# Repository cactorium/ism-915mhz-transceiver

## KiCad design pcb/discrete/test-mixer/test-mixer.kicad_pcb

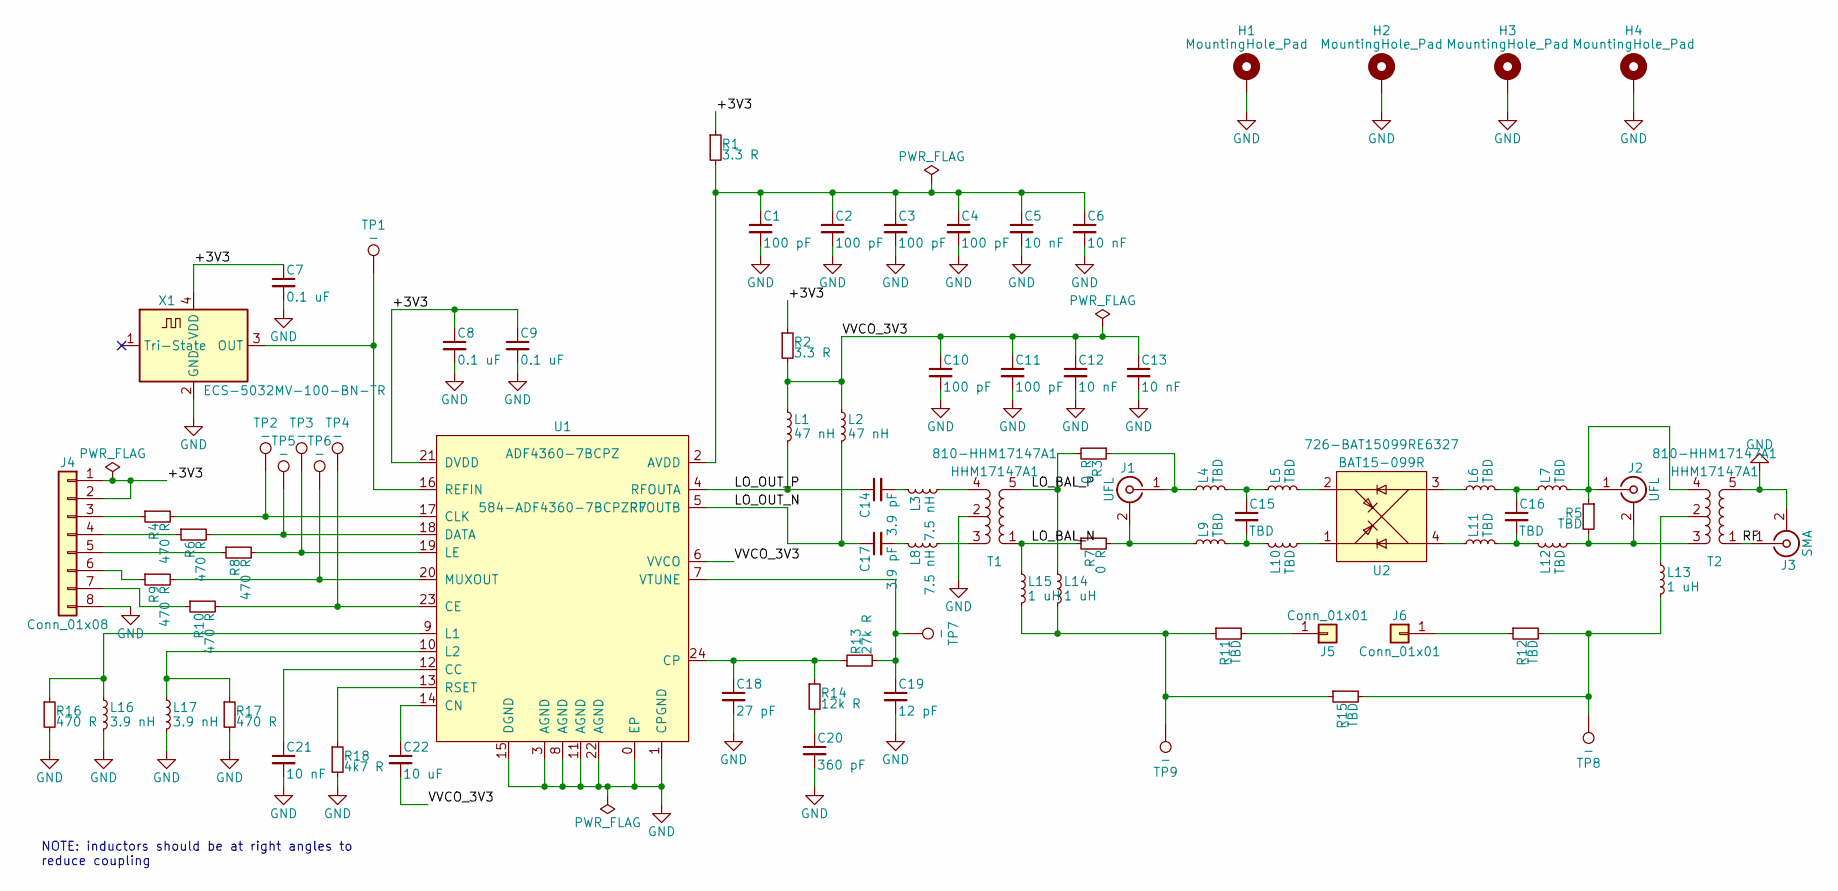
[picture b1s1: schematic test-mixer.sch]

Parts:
C1, C2, C3, C4, C10, C11: 100 pF; C_0603_1608Metric_Pad1.05x0.95mm_HandSolder; Mouser 791-RF18N101J500CT
C5, C6, C12, C13, C21: 10 nF; C_0402_1005Metric; Mouser 80-C0402C103K4R7411
C7, C8, C9: 0.1 uF; C_0402_1005Metric; Mouser 80-C0402C104M4P
C14, C17: 3.9 pF; C_0402_1005Metric; Mouser 81-GJM1555C1H3R9CB1D
C15, C16: TBD; C_0402_1005Metric; Mouser NoPart
C18: 27 pF; C_0603_1608Metric_Pad1.05x0.95mm_HandSolder; Mouser 80-C0603C270K5G
C19: 12 pF; C_0805_2012Metric_Pad1.15x1.40mm_HandSolder; Mouser 80-C0805C120J1HACTU
C20: 360 pF; C_0402_1005Metric; Mouser 963-UMK105CH361JVHF
C22: 10 uF; C_0805_2012Metric_Pad1.15x1.40mm_HandSolder; Mouser 81-GRM21BC81C106KE5L
H1, H2, H3, H4: MountingHole_Pad; MountingHole_3.2mm_M3_DIN965; Mouser NoPart
J1, J2: UFL; 2337019-1; Mouser 571-2337019-1
J3: SMA; 142-0701-801-with-taper; Mouser 530-142-0701-801
J4: Conn_01x08; PinHeader_1x08_P2.54mm_Vertical; Mouser NoPart
J5, J6: Conn_01x01; PinSocket_1x01_P2.54mm_Vertical; Mouser NoPart
L1, L2: 47 nH; C_0402_1005Metric; Mouser 81-LQG15HZ47NJ02D
L3, L8: 7.5 nH; C_0402_1005Metric; Mouser 81-LQG15HN7N5J02D
L4, L5, L6, L7, L9, L10, L11, L12: TBD; C_0402_1005Metric; Mouser NoPart
L13, L14, L15: 1 uH; C_0402_1005Metric; Mouser 815-AIML-0402-1R0KT
L16, L17: 3.9 nH; C_0402_1005Metric; Mouser 81-LQG15HS3N9C02D
R1, R2: 3.3 R; R_0603_1608Metric_Pad1.05x0.95mm_HandSolder; Mouser 652-CR0603-J/-3R3ELF
R3, R7: 0 R; R_0402_1005Metric; Mouser 71-CRCW04020000Z0EDC
R4, R6, R8, R9, R10, R16, R17: 470 R; R_0402_1005Metric; Mouser 603-RC0402JR-13470RL
R5, R11, R12, R15: TBD; R_0402_1005Metric; Mouser NoPart
R13: 27k R; R_0603_1608Metric_Pad1.05x0.95mm_HandSolder; Mouser 603-RC0603FR-1027KL
R14: 12k R; R_0603_1608Metric_Pad1.05x0.95mm_HandSolder; Mouser 652-CR0603FX-1202ELF
R18: 4k7 R; R_0402_1005Metric; Mouser 603-AC0402FR-134K7L
T1, T2: HHM17147A1; TDK_HHM17147A1; Mouser 810-HHM17147A1
TP1, TP2, TP3, TP4, TP5, TP6, TP7, TP8, TP9: -; TestPoint_Pad_D1.0mm; Mouser NoPart
U1: ADF4360-7BCPZ; Analog_CP-24-14; Mouser 584-ADF4360-7BCPZR7
U2: BAT15-099R; NXP_SOT143B; Mouser 726-BAT15099RE6327
X1: ECS-5032MV-100-BN-TR; Oscillator_SMD_SeikoEpson_SG8002LB-4Pin_5.0x3.2mm_HandSolde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; Mouser 520-5032MV-100-BNT

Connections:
/+3V3: C7.1, C8.1, C9.1, J4.1, J4.2, R1.1, R2.1, U1.21 (DVDD), X1.4 (VDD)
/LO_BAL_N: L15.1, R7.1, T1.1 (SINGLE)
/LO_BAL_P: L14.1, R3.2, T1.5 (GND)
/LO_OUT_N: C17.1, L2.2, U1.5 (RFOUTB)
/LO_OUT_P: C14.1, L1.2, U1.4 (RFOUTA)
/RF: J3.1 (In), T2.1 (SINGLE)
/VVCO_3V3: C10.1, C11.1, C12.1, C13.1, C22.2, L1.1, L2.1, R2.2, U1.6 (VVCO)
GND: C1.2, C2.2, C3.2, C4.2, C5.2, C6.2, C7.2, C8.2, C9.2, C10.2, C11.2, C12.2, C13.2, C18.2, C19.2, C20.2, C21.2, H1.1, H2.1, H3.1, H4.1, J3.2 (Ext), J4.8, L16.2, L17.2, R16.2, R17.2, R18.2, T1.2 (COMMON), T2.5 (GND), U1.0 (EP), U1.1 (CPGND), U1.3 (AGND), U1.8 (AGND), U1.11 (AGND), U1.15 (DGND), U1.22 (AGND), X1.2 (GND)
unnamed: C1.1, C2.1, C3.1, C4.1, C5.1, C6.1, R1.2, U1.2 (AVDD)
unnamed: C14.2, L3.1
unnamed: C15.1, L4.2, L5.1
unnamed: C15.2, L9.2, L10.1
unnamed: C16.1, L6.2, L7.1
unnamed: C16.2, L11.2, L12.1
unnamed: C17.2, L8.1
unnamed: C18.1, R13.1, R14.1, U1.24 (CP)
unnamed: C19.1, R13.2, TP7.1, U1.7 (VTUNE)
unnamed: C20.1, R14.2
unnamed: C21.1, U1.12 (CC)
unnamed: C22.1, U1.14 (CN)
unnamed: J1.1 (In), L4.1, R3.1
unnamed: J1.2 (Ext), L9.1, R7.2
unnamed: J2.1 (In), L7.2, R5.1, T2.4 (-)
unnamed: J2.2 (Ext), L12.2, R5.2, T2.3 (+)
unnamed: J4.3, R4.1
unnamed: J4.4, R6.1
unnamed: J4.5, R8.1
unnamed: J4.6, R9.1
unnamed: J4.7, R10.1
unnamed: J5.1, R11.2
unnamed: J6.1, R12.1
unnamed: L3.2, T1.4 (-)
unnamed: L5.2, U2.2 (B)
unnamed: L6.1, U2.3 (C)
unnamed: L8.2, T1.3 (+)
unnamed: L10.2, U2.1 (A)
unnamed: L11.1, U2.4 (D)
unnamed: L13.1, T2.2 (COMMON)
unnamed: L13.2, R12.2, R15.2, TP8.1
unnamed: L14.2, L15.2, R11.1, R15.1, TP9.1
unnamed: L16.1, R16.1, U1.9 (L1)
unnamed: L17.1, R17.1, U1.10 (L2)
unnamed: R4.2, TP2.1, U1.17 (CLK)
unnamed: R6.2, TP5.1, U1.18 (DATA)
unnamed: R8.2, TP3.1, U1.19 (LE)
unnamed: R9.2, TP6.1, U1.20 (MUXOUT)
unnamed: R10.2, TP4.1, U1.23 (CE)
unnamed: R18.1, U1.13 (RSET)
unnamed: TP1.1, U1.16 (REFIN), X1.3 (OUT)

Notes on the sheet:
NOTE: inductors should be at right angles to reduce coupling

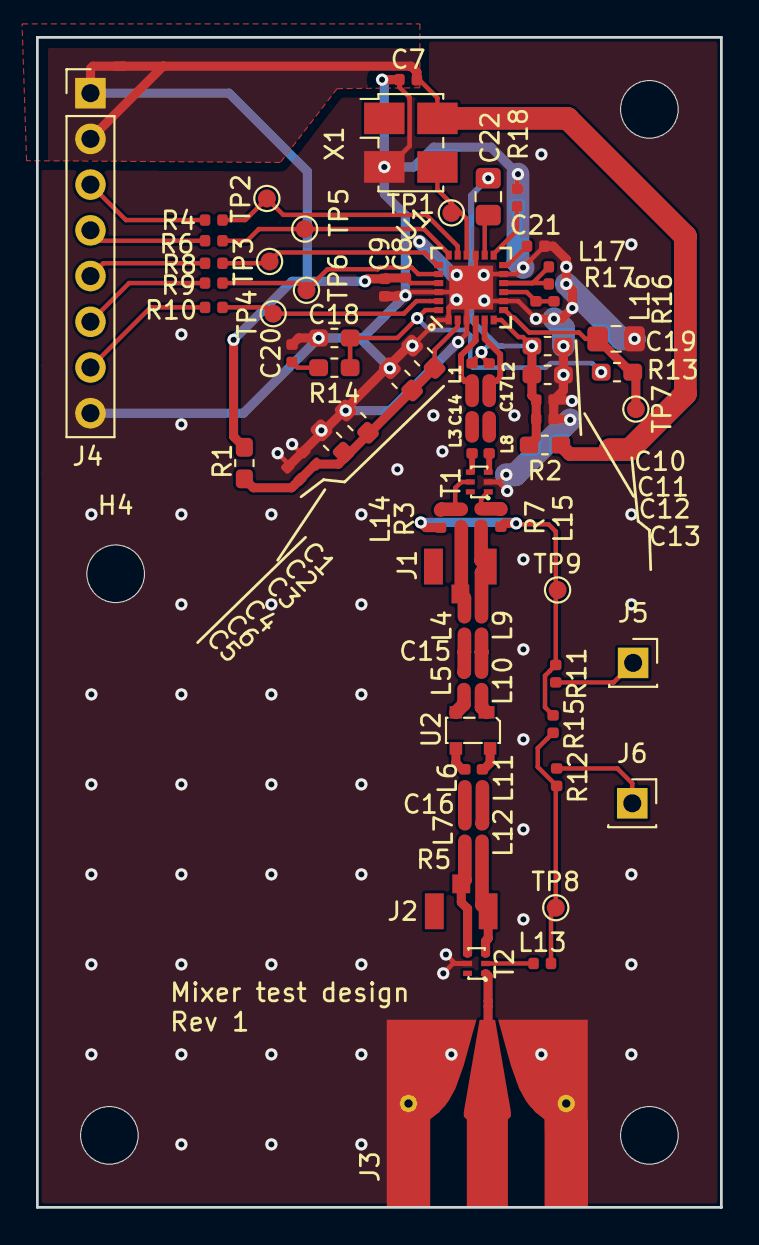
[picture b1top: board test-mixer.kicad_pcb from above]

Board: 2 copper layers, 38.0 x 65.0 mm, 81 parts (0 on the bottom side), 49 nets.

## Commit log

2019-03-19 Work on power amplifier design; got the matching networks set up, and they seem to work, a part from being almost marginally unstable
2019-03-19 Test out cascading them to get more gain
2019-03-19 Add NXP BFU520 scattering parameters
2019-04-13 Start work on schematics
2019-04-13 Start work on power amplifier stage and LO amplifier
2019-04-13 Add SPICE models for BFU520*
2019-04-13 Ignore QUCS-generated files
2019-04-13 LO amplifier simulation is pretty close to done; it seems like the BFU520XR will just barely do the job; compression point is >6 dBm, amplifier seems sufficiently stable
2019-04-13 Finish first draft of LO amplifier
2019-04-14 Copy in qucs Python files to process Qucs data in Python
2019-04-14 Move qucsdata to the right directory
2019-04-14 Match mixer LO input and RF output to 50 ohms
2019-04-15 Finish active mixer simulation; it looks good!
2019-04-17 Finish diode mixer simulations and capture in schematic
2019-04-18 Fix scattering parameter phase calculations
2019-04-29 Capture IF amplifier stages and work on LNA stages
2019-05-01 Picked matched NPNs for IF amplifier stages
2019-05-14 Work on LNA design; looks like minimal matching produces the best results
2019-05-17 Almost working LNA first and second stage; need to figure out why the second stage isn't conjugatively matching correctly
2019-05-17 Second stage almost working, still off for some reason
2019-05-18 Fix typo that was messing up conjugate match calculations
2019-05-18 Lower bias current to 5 mA
2019-06-19 Save changes while moving over to the new laptop
2019-06-19 Fix symbol tables I guess
2019-06-26 Finish TX mixer; added IF buffer
2019-06-28 Update so that it works witth the current scikit-rf master; TODO figure out how to version scikit-rf
2019-06-30 Work on LNA staging, attenuator design, various fixes elsewhere
2019-06-30 Rerun low_noise.ipynb using more accurate Vce value
2019-07-05 Test out noisy series operations; at least the function runs successfully
2019-07-05 Play around with optimizing degenerative inductor value
2019-07-05 Optimize against NF directly
2019-07-06 Woo, the degenerated design works but probably isn't worthwhile because of the gain loss
2019-07-12 Work on simulations a litte more.. looks like testing in-situ is honestly the best option
2019-09-13 Source hybrid quadrature coupler, add front end LC filter
2019-09-13 Design DAC/ADC stages, pass out all control signals to top sheet
2019-09-16 Wire out all control signals to connectors TODO PLL charge pump loop, bypass caps in attenuator circuit, antialiasing filter for ADC frontend
2019-09-17 Start work in footprinting everything
2019-09-17 Fix some parts
2019-09-18 The footprintening continues
2019-09-18 Add matching PNP/NPN transistor pairs, fix pin numbering for BFU520R transistors TODO fix biasing on power stage, source last NPN transistor, autofill and start sourcing passives
2019-09-19 All component values set (TODO change transistor gain stages to match values from experimentation
2019-09-19 Autofill; lots left to do
2019-09-19 Autofill all; TODO improve formatting on autofill_all output
2019-09-20 Footprint some stuff
2019-09-20 Autofill
2019-09-20 Add more footprints, saving before autofill
2019-09-23 Reannotate everything; I'm trying to cut down the number of components
2019-09-24 Footprint a lot of stuff; save before autofill
2019-09-24 Add in a couple more components, save before autofill
2019-09-24 Footprint more stuff
2019-09-25 Start work on simpler RF board using less discrete components so it's not a giant mess
2019-10-01 Fix mixer simulation and start work on test mixer PCB
2019-10-03 Footprint everything(?)
2019-10-03 Move test mixer files down a directory
2019-10-03 Remove old project
2019-10-03 Add in some more footprints before autofill
2019-10-03 Autofill finish
2019-10-03 Add mounting holes, fix DRC errors
2019-10-05 Finish layout
2019-12-19 Generate Gerbers and BOM
2019-12-20 Regenerate Gerbers, just to be safe
2019-12-20 Regenerate in old format
